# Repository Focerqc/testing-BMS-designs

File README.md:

# Testing BMS designs

Experimental battery-management hardware, built in public. The first design is an
**18S cell-monitoring slave module** based on the Analog Devices **ADBMS1818**,
talking to a separate, bought master over isoSPI.

> Engineering drafts. Nothing here is validated for manufacture or use on a real pack.

## Status (2026-11-13)

| | **18S Guard** (`slave-18s/`) | **18S Lean** (`slave-18s-lean/`) |
|---|---|---|
| Purpose | Hot-plug harnesses, unknown packs, bench work | One known 18S pack, harness plugged in once |
| Schematic | Complete, ERC 0 / 0 | Generated from Guard, ERC 0 / 0 |
| PCB | 120 × 70 mm placeholder, parts grouped, **not routed** | **70 × 32 mm, 4 layers, fully routed**, every part on the front |
| Ready to order | No | **No.** The isoSPI area is being re-planned (see below) |

Lean is the board being worked on. Guard is its source: Lean's schematic is generated from
Guard by `_tools/kicad_sch/make_lean.py` and is never edited by hand.

### Lean at a glance

- 77 footprints, 88 nets, single-sided assembly, four M2 holes.
- Cell plugs: JST PH, **10 + 9 pins**. J1 carries C0–C9 and J5 carries C10–C18, so C9 comes in
  on one wire and the two plugs can be told apart.
- Per cell: a 10 Ω 0402 series resistor and a 120 Ω 1206 balance resistor (about 31 mA and
  0.12 W at 4.2 V) through the chip's internal switches.
- Regulator: FZT853 (SOT-223) driven by the chip, with a 1 kΩ 1 W collector resistor that
  takes part of the heat off the transistor.
- isoSPI: two Bourns SM91502AL transformers, split 2 × 51 Ω termination with 10 nF
  centre-tap capacitors, JST GH 2-pin plugs.
- No fuses, clamps, TVS or C-pin capacitors. Those are Guard's.

Its checks on this branch: netlist 239 pins with 0 problems, PCB parity pass, design rules
loaded, and zone-filled DRC with 0 errors, 0 unconnected items and 153 silkscreen warnings.

## What we have learned so far

### 1. A clean DRC does not make an isoSPI layout right

The ADBMS1818 datasheet (Rev. B, p. 86) asks for two things that DRC cannot see: no ground
plane under or between the transformer and its plug, and **no trace crossing an isoSPI line**
unless a ground plane on an inner layer separates them. Lean meets the first with keep-out
rules. For the second we wrote `_tools/kicad_sch/isospi_shield_check.py`.

- The first version of that check reported 6 crossings. It looked only at the transformer
  centre-tap and termination nets and never treated the chip-side pairs (IPA/IMA, IPB/IMB) as
  isoSPI lines. With each port grouped properly it finds **20**: 12 where port A crosses
  port B, and 8 where the top-of-stack supply track (CELL18) crosses either port.
  The lesson: check a checker against the circuit before trusting its number.
- **Rerouting cannot remove them.** Both ports sit side by side in one corner. Port A's pins
  are below port B's on the chip and its transformer is the far one, so port A has to get
  past port B. Port B fills the whole height from its plug at the board edge down to the
  regulator copper, and the rules keep other tracks out from under its transformer. The best
  a reroute can do is 10 crossings.
- The top-of-stack supply has the same problem: it starts above both ports and ends at the
  regulator below them.

### 2. Put the two isoSPI ports at opposite ends

We compared three other slave boards of this kind. Every one of them puts its two isoSPI ports
at **opposite ends of the board**, each plug with its transformer right beside it. Lean is the
only one that groups them. Splitting them means:

- each port runs from its pins to its own end, so the ports never meet;
- the daisy-chain cables leave from opposite ends instead of crossing over the board;
- the regulator and the top-of-stack supply can be kept clear of both ports.

**Planned next step:** a new Lean floorplan with one port at each end. It moves parts, so it
is tried on a scratch copy first.

### 3. What turned 120 × 70 mm into 70 × 32 mm

- Four copper layers instead of two.
- Small series resistors (the 10 Ω parts carry almost no current) and 120 Ω 1206 balance
  resistors instead of 33 Ω 2512.
- Smaller isoSPI transformers, GH plugs, M2 holes and no test points.
- Leaving out the hot-plug protection, which is the Guard/Lean split.
- Routing planned as lanes before any track is drawn, then written by script from the pad
  positions (`lean_place.py`, `lean_route.py`), so a placement change can be routed and
  checked again in minutes.

### 4. The regulator is a heat question, not a fit question

At 75.6 V the linear regulator dissipates about 1.55 W at 22 mA and 2.5 W at 35 mA, whatever
the package. The 1 kΩ collector resistor only moves part of that off the transistor (about
0.48 W of the 1.55 W). Whether the board stays cool enough is still open. It needs the
master's real duty cycle or a measurement.

### 5. Working method

- One source schematic and generated variants. Part swaps for Lean live in one table.
- `kicad-cli` is the ground truth for netlist, ERC and DRC. Every schematic or PCB change is
  followed by the same scripted checks (below).
- Size and placement changes are tried on a scratch copy before the real board.
- The tool-by-tool lessons are in [AGENTS.md](AGENTS.md).

## Open before Lean can be ordered

- [ ] isoSPI floorplan with the ports at opposite ends, then 0 crossings in the check.
- [ ] Regulator thermal acceptance (see 4).
- [ ] The assembler's acceptance of the open 0.2 mm vias in the chip's exposed pad.
- [ ] Silkscreen cleanup (153 warnings).
- [ ] Harness: match the plug pin order to the pack's tap and thermistor wiring. Seen from
      above with the cell plugs along the top edge, pin 1 of both is at the left end.
- [ ] Bench test with a cell simulator and one master. Hot-plugging is not qualified on Lean.

The full list, with reasons and dates, is in
[docs/slave-18s-design-basis.md](docs/slave-18s-design-basis.md).

## Checks

```
"C:\Program Files\KiCad\10.0\bin\python.exe" _tools/kicad_sch/lean_route.py --dry
python _tools/kicad_sch/check_slave18s.py --variant lean
python _tools/kicad_sch/check_pcb_parity.py --variant lean
python _tools/kicad_sch/make_rules.py --variant lean --check
python _tools/kicad_sch/isospi_shield_check.py
```

Then run `kicad-cli pcb drc --severity-all --refill-zones` on the board.

## Layout of this repository

| Path | What it is |
|---|---|
| `slave-18s/` | **18S Guard**: KiCad 10 project with hot-plug protection (fuses, clamps, TVS, C-pin caps, test points) |
| `slave-18s-lean/` | **18S Lean**: the same slave without them, 70 × 32 mm, 4 layers. Schematic generated by `make_lean.py`; placement and routing written by `lean_place.py` and `lean_route.py` |
| `docs/slave-18s-design-basis.md` | Values, reasoning, deviations from the datasheet circuit and open items |
| `docs/slave-18s-lean-layout-plan.md` | Placement and routing plan for Lean, with the check to run after each step |
| `docs/master-ennoid-xlite.md` | The bought master and how the slave fits under it |
| `_tools/kicad_sch/` | Checks, design-rule generator, Lean generator, placement and routing scripts (table in AGENTS.md) |
| `_tools/pcb_dashboard/` | Board Boxes: local KiCad dashboard (top and bottom view, annotate, chip info, fresh 3D renders) |
| `site/` | Published GitHub Pages copy of Board Boxes plus the News page |
| `_reference/` | Datasheets and reference material. The private parts are gitignored |

## Dashboards

- **Local:** double-click `Start Dashboards.cmd` (Python with `requirements.txt`, KiCad 10).
  Opens http://localhost:5180/.
- **Hosted:** https://focerqc.github.io/testing-BMS-designs/ (News at `news.html`).

Refresh the hosted copy:

```
python _tools/pcb_dashboard/export_site.py
node _tools/pcb_dashboard/check_hosted.cjs
```

Then push `site/` to `main`; `.github/workflows/pages.yml` publishes it.

## Roadmap

1. ~~18S slave schematic from the ADBMS1818 typical application.~~ Done.
2. Slave PCB: Lean is routed. Redo its isoSPI floorplan, then order and bench test with a
   resistor-ladder cell simulator and an LTC6820/ESP32 dongle.
3. Carrier PCB taking two slaves (target slot 156.5 × 37 × 10 mm) for a plug-and-play harness.
4. Master: bought, not designed here (see `docs/master-ennoid-xlite.md`).

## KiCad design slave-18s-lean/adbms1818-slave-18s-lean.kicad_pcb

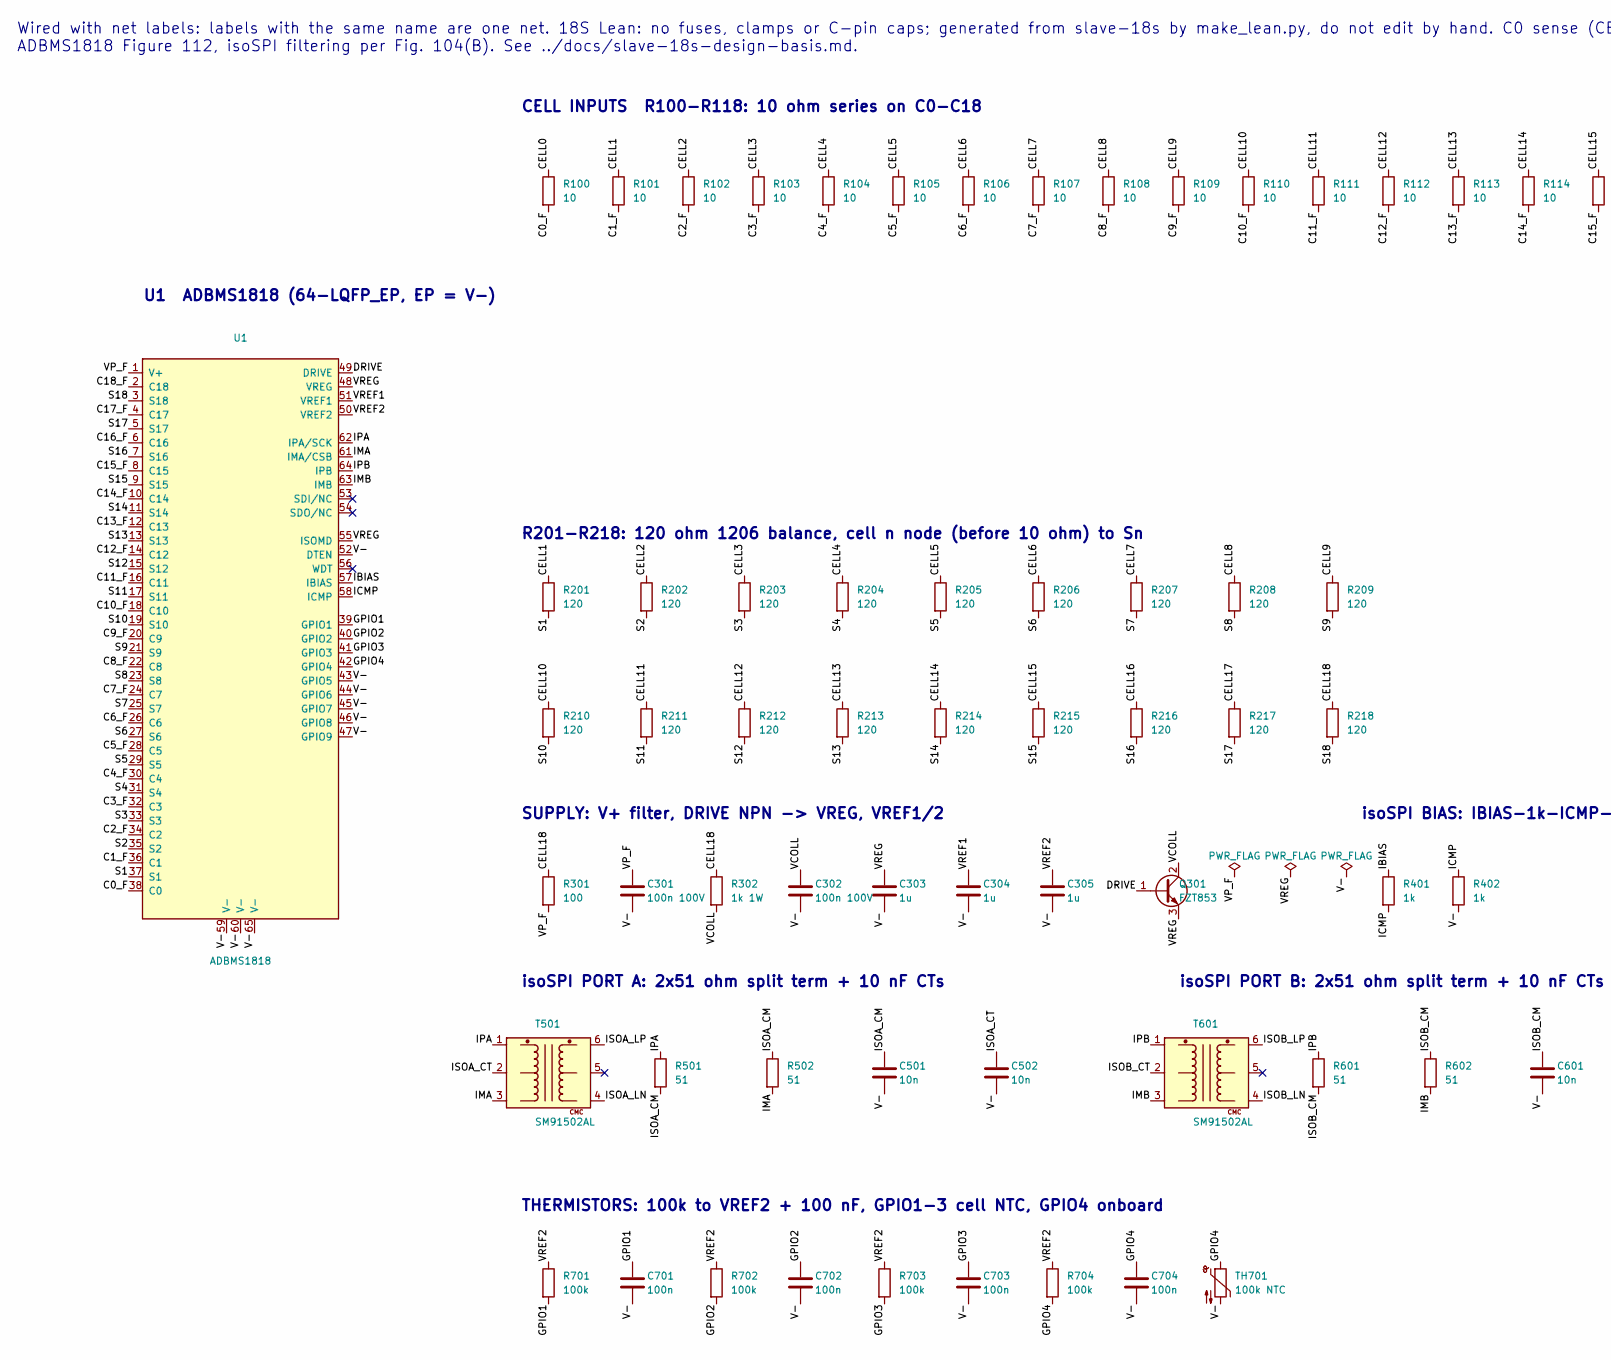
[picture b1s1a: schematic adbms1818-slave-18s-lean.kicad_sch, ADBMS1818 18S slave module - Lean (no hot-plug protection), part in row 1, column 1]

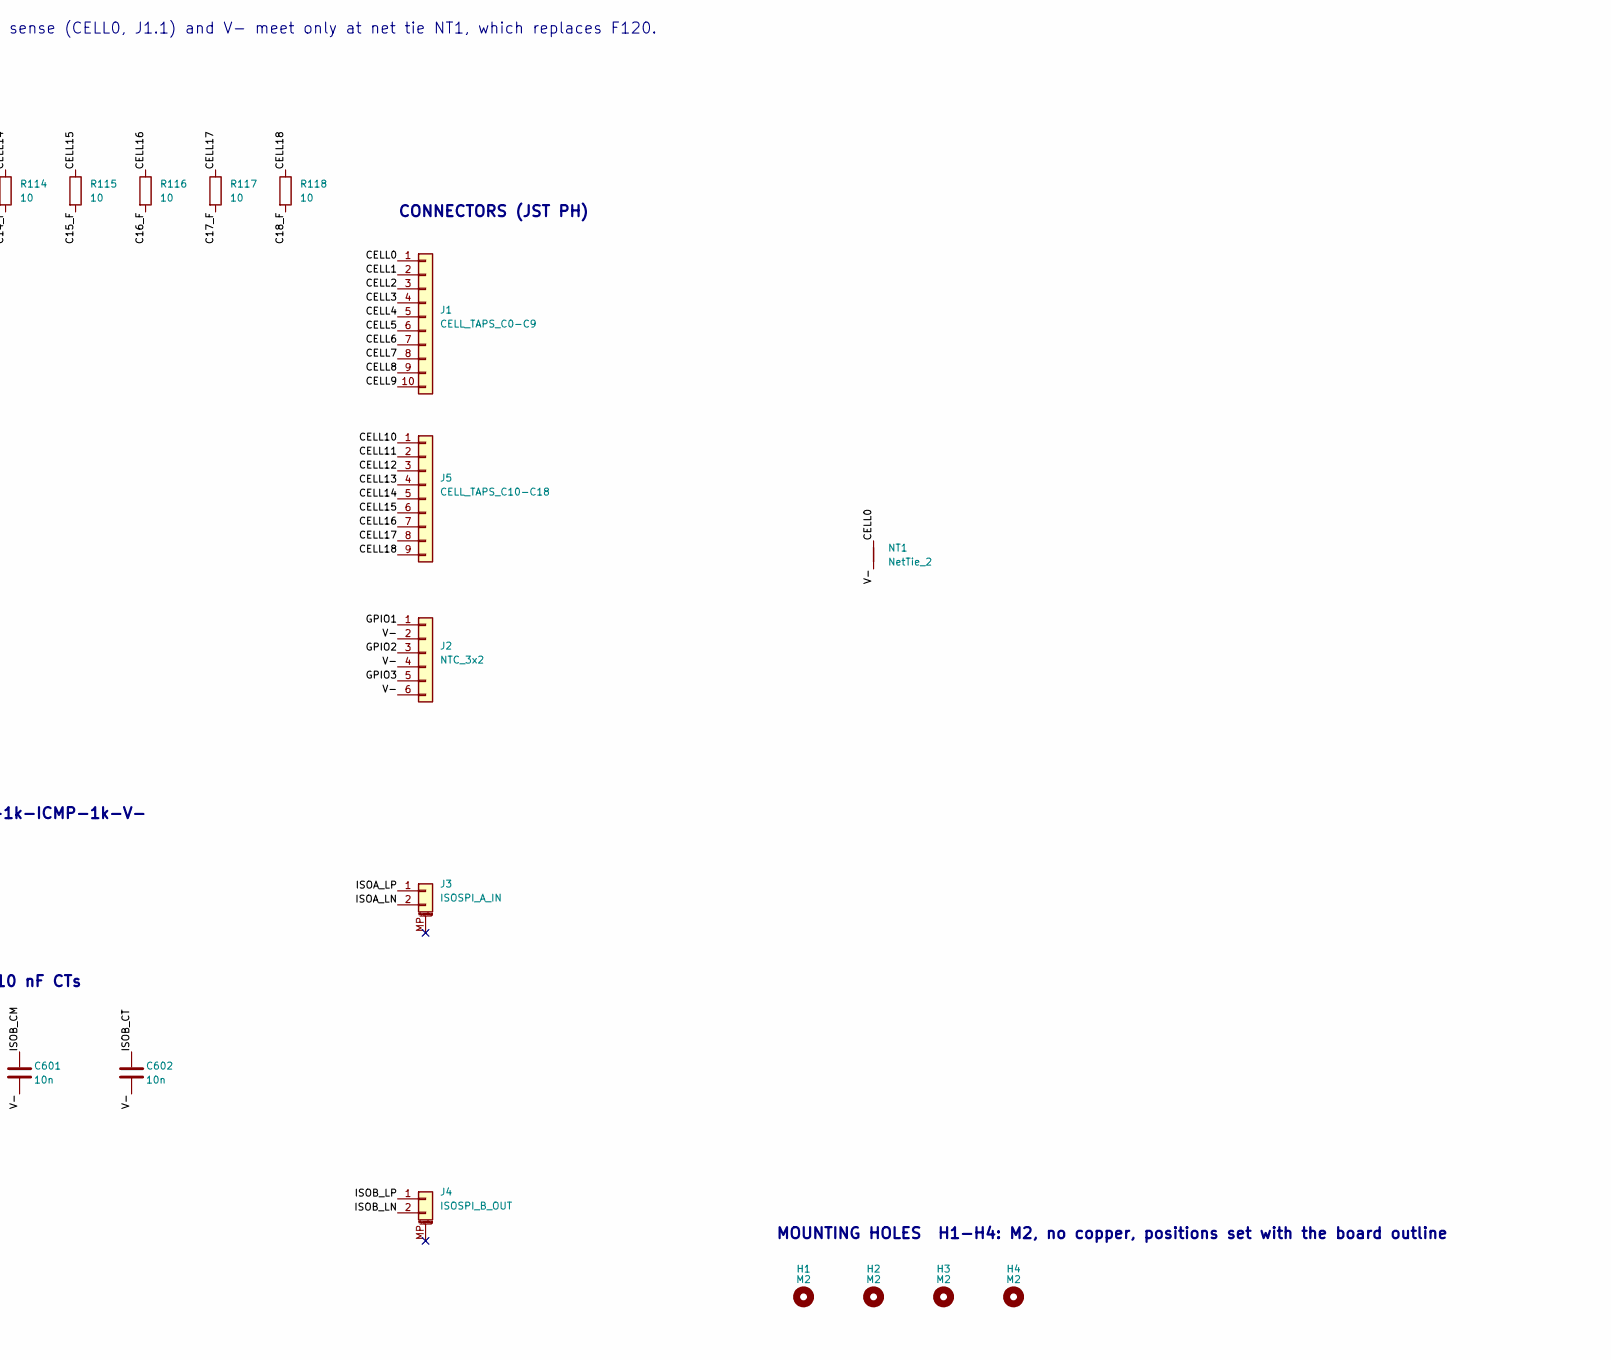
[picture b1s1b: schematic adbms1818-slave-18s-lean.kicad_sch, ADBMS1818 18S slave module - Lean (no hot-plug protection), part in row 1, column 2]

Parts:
C301, C302: 100n 100V; C_0805_2012Metric; MPN CL21B104KCFNNNE; LCSC C28233
C303, C304, C305: 1u; C_0603_1608Metric; MPN CL10A105KB8NNNC; LCSC C15849
C501, C502: 10n; C_0603_1608Metric; MPN 0603B103K500NT; LCSC C57112
C601, C602: 10n; C_0402_1005Metric; MPN CL05B103KB5NNNC; LCSC C15195
C701, C702, C703, C704: 100n; C_0603_1608Metric; MPN CC0603KRX7R9BB104; LCSC C14663
H1, H2, H3, H4: M2; MountingHole_2.2mm_M2
J1: CELL_TAPS_C0-C9; JST_PH_B10B-PH-K_1x10_P2.00mm_Vertical; MPN B10B-PH-K-S(LF)(SN); LCSC C158038
J2: NTC_3x2; JST_PH_B6B-PH-K_1x06_P2.00mm_Vertical; MPN B6B-PH-K-S(LF)(SN); LCSC C131342
J3: ISOSPI_A_IN; JST_GH_BM02B-GHS-TBT_1x02-1MP_P1.25mm_Vertical; MPN BM02B-GHS-TBT(LF)(SN); LCSC C161690
J4: ISOSPI_B_OUT; JST_GH_BM02B-GHS-TBT_1x02-1MP_P1.25mm_Vertical; MPN BM02B-GHS-TBT(LF)(SN); LCSC C161690
J5: CELL_TAPS_C10-C18; JST_PH_B9B-PH-K_1x09_P2.00mm_Vertical; MPN B9B-PH-K-S(LF)(SN); LCSC C157968
NT1: NetTie_2; NetTie-2_SMD_Pad0.5mm
Q301: FZT853; SOT-223-3_TabPin2; MPN FZT853TA; LCSC C435890
R100, R101, R102, R103, R104, R105, R106, R107, R108, R109, R110, R111, R112, R113, R114, R115, R116, R117, R118: 10; R_0402_1005Metric; MPN 0402WGF100JTCE; LCSC C25077
R201, R202, R203, R204, R205, R206, R207, R208, R209, R210, R211, R212, R213, R214, R215, R216, R217, R218: 120; R_1206_3216Metric; MPN 1206W4F1200T5E; LCSC C17909
R301: 100; R_0603_1608Metric; MPN 0603WAF1000T5E; LCSC C22775
R302: 1k 1W; R_2512_6332Metric; MPN 25121WF1001T4E; LCSC C54315
R401, R402: 1k; R_0603_1608Metric; MPN 0603WAF1001T5E; LCSC C21190
R501, R502: 51; R_0603_1608Metric; MPN 0603WAF510JT5E; LCSC C23197
R601, R602: 51; R_0402_1005Metric; MPN 0402WGF510JTCE; LCSC C25125
R701, R702, R703, R704: 100k; R_0603_1608Metric; MPN 0603WAF1003T5E; LCSC C25803
T501, T601: SM91502AL; Bourns_SM91502AL; MPN SM91502ALE; LCSC C915690
TH701: 100k NTC; R_0603_1608Metric; MPN NCP18WF104F12RB; LCSC C71280
U1: ADBMS1818; LQFP-64-1EP_10x10mm_P0.5mm_EP5x5mm_ThermalVias; MPN ADBMS1818ASWAZ-RL; LCSC C5372802

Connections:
/C0_F: R100.2, U1.38 (C0)
/C1_F: R101.2, U1.36 (C1)
/C2_F: R102.2, U1.34 (C2)
/C3_F: R103.2, U1.32 (C3)
/C4_F: R104.2, U1.30 (C4)
/C5_F: R105.2, U1.28 (C5)
/C6_F: R106.2, U1.26 (C6)
/C7_F: R107.2, U1.24 (C7)
/C8_F: R108.2, U1.22 (C8)
/C9_F: R109.2, U1.20 (C9)
/C10_F: R110.2, U1.18 (C10)
/C11_F: R111.2, U1.16 (C11)
/C12_F: R112.2, U1.14 (C12)
/C13_F: R113.2, U1.12 (C13)
/C14_F: R114.2, U1.10 (C14)
/C15_F: R115.2, U1.8 (C15)
/C16_F: R116.2, U1.6 (C16)
/C17_F: R117.2, U1.4 (C17)
/C18_F: R118.2, U1.2 (C18)
/CELL0: J1.1, NT1.1, R100.1
/CELL1: J1.2, R101.1, R201.1
/CELL2: J1.3, R102.1, R202.1
/CELL3: J1.4, R103.1, R203.1
/CELL4: J1.5, R104.1, R204.1
/CELL5: J1.6, R105.1, R205.1
/CELL6: J1.7, R106.1, R206.1
/CELL7: J1.8, R107.1, R207.1
/CELL8: J1.9, R108.1, R208.1
/CELL9: J1.10, R109.1, R209.1
/CELL10: J5.1, R110.1, R210.1
/CELL11: J5.2, R111.1, R211.1
/CELL12: J5.3, R112.1, R212.1
/CELL13: J5.4, R113.1, R213.1
/CELL14: J5.5, R114.1, R214.1
/CELL15: J5.6, R115.1, R215.1
/CELL16: J5.7, R116.1, R216.1
/CELL17: J5.8, R117.1, R217.1
/CELL18: J5.9, R118.1, R218.1, R301.1, R302.1
/DRIVE: Q301.1 (B), U1.49 (DRIVE)
/GPIO1: C701.1, J2.1, R701.2, U1.39 (GPIO1)
/GPIO2: C702.1, J2.3, R702.2, U1.40 (GPIO2)
/GPIO3: C703.1, J2.5, R703.2, U1.41 (GPIO3)
/GPIO4: C704.1, R704.2, TH701.1, U1.42 (GPIO4)
/IBIAS: R401.1, U1.57 (IBIAS)
/ICMP: R401.2, R402.1, U1.58 (ICMP)
/IMA: R502.2, T501.3 (PHY-), U1.61 (IMA/CSB)
/IMB: R602.2, T601.3 (PHY-), U1.63 (IMB)
/IPA: R501.1, T501.1 (PHY+), U1.62 (IPA/SCK)
/IPB: R601.1, T601.1 (PHY+), U1.64 (IPB)
/ISOA_CM: C501.1, R501.2, R502.1
/ISOA_CT: C502.1, T501.2 (PHY_CT)
/ISOA_LN: J3.2, T501.4 (LINE-)
/ISOA_LP: J3.1, T501.6 (LINE+)
/ISOB_CM: C601.1, R601.2, R602.1
/ISOB_CT: C602.1, T601.2 (PHY_CT)
/ISOB_LN: J4.2, T601.4 (LINE-)
/ISOB_LP: J4.1, T601.6 (LINE+)
/S1: R201.2, U1.37 (S1)
/S2: R202.2, U1.35 (S2)
/S3: R203.2, U1.33 (S3)
/S4: R204.2, U1.31 (S4)
/S5: R205.2, U1.29 (S5)
/S6: R206.2, U1.27 (S6)
/S7: R207.2, U1.25 (S7)
/S8: R208.2, U1.23 (S8)
/S9: R209.2, U1.21 (S9)
/S10: R210.2, U1.19 (S10)
/S11: R211.2, U1.17 (S11)
/S12: R212.2, U1.15 (S12)
/S13: R213.2, U1.13 (S13)
/S14: R214.2, U1.11 (S14)
/S15: R215.2, U1.9 (S15)
/S16: R216.2, U1.7 (S16)
/S17: R217.2, U1.5 (S17)
/S18: R218.2, U1.3 (S18)
/V-: C301.2, C302.2, C303.2, C304.2, C305.2, C501.2, C502.2, C601.2, C602.2, C701.2, C702.2, C703.2, C704.2, J2.2, J2.4, J2.6, NT1.2, R402.2, TH701.2, U1.43 (GPIO5), U1.44 (GPIO6), U1.45 (GPIO7), U1.46 (GPIO8), U1.47 (GPIO9), U1.52 (DTEN), U1.59 (V-), U1.60 (V-), U1.65 (V-)
/VCOLL: C302.1, Q301.2 (C), R302.2
/VP_F: C301.1, R301.2, U1.1 (V+)
/VREF1: C304.1, U1.51 (VREF1)
/VREF2: C305.1, R701.1, R702.1, R703.1, R704.1, U1.50 (VREF2)
/VREG: C303.1, Q301.3 (E), U1.48 (VREG), U1.55 (ISOMD)

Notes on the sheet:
R201-R218: 120 ohm 1206 balance, cell n node (before 10 ohm) to Sn
CONNECTORS (JST PH)
CELL INPUTS R100-R118: 10 ohm series on C0-C18
Wired with net labels: labels with the same name are one net. 18S Lean: no fuses, clamps or C-pin caps; generated from slave-18s by make_lean.py, do not edit by hand. C0 sense (CELL0, J1.1) and V- meet only at net tie NT1, which replaces F120. ADBMS1818 Figure 112, isoSPI filtering per Fig. 104(B).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
THERMISTORS: 100k to VREF2 + 100 nF, GPIO1-3 cell NTC, GPIO4 onboard
isoSPI BIAS: IBIAS-1k-ICMP-1k-V-
U1 ADBMS1818 (64-LQFP_EP, EP = V-)
MOUNTING HOLES H1-H4: M2, no copper, positions set with the board outline
isoSPI PORT A: 2x51 ohm split term + 10 nF CTs
isoSPI PORT B: 2x51 ohm split term + 10 nF CTs
SUPPLY: V+ filter, DRIVE NPN -> VREG, VREF1/2

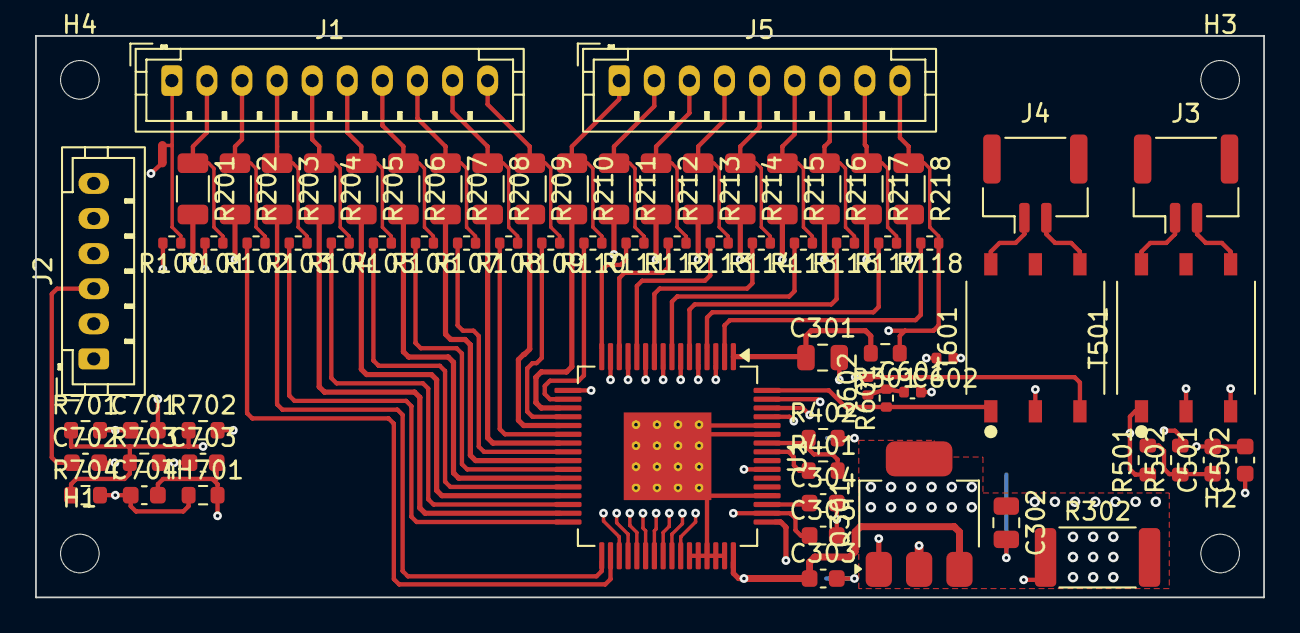
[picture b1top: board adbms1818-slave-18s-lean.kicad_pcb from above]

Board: 4 copper layers, 70.0 x 32.0 mm, 77 parts (0 on the bottom side), 81 nets.

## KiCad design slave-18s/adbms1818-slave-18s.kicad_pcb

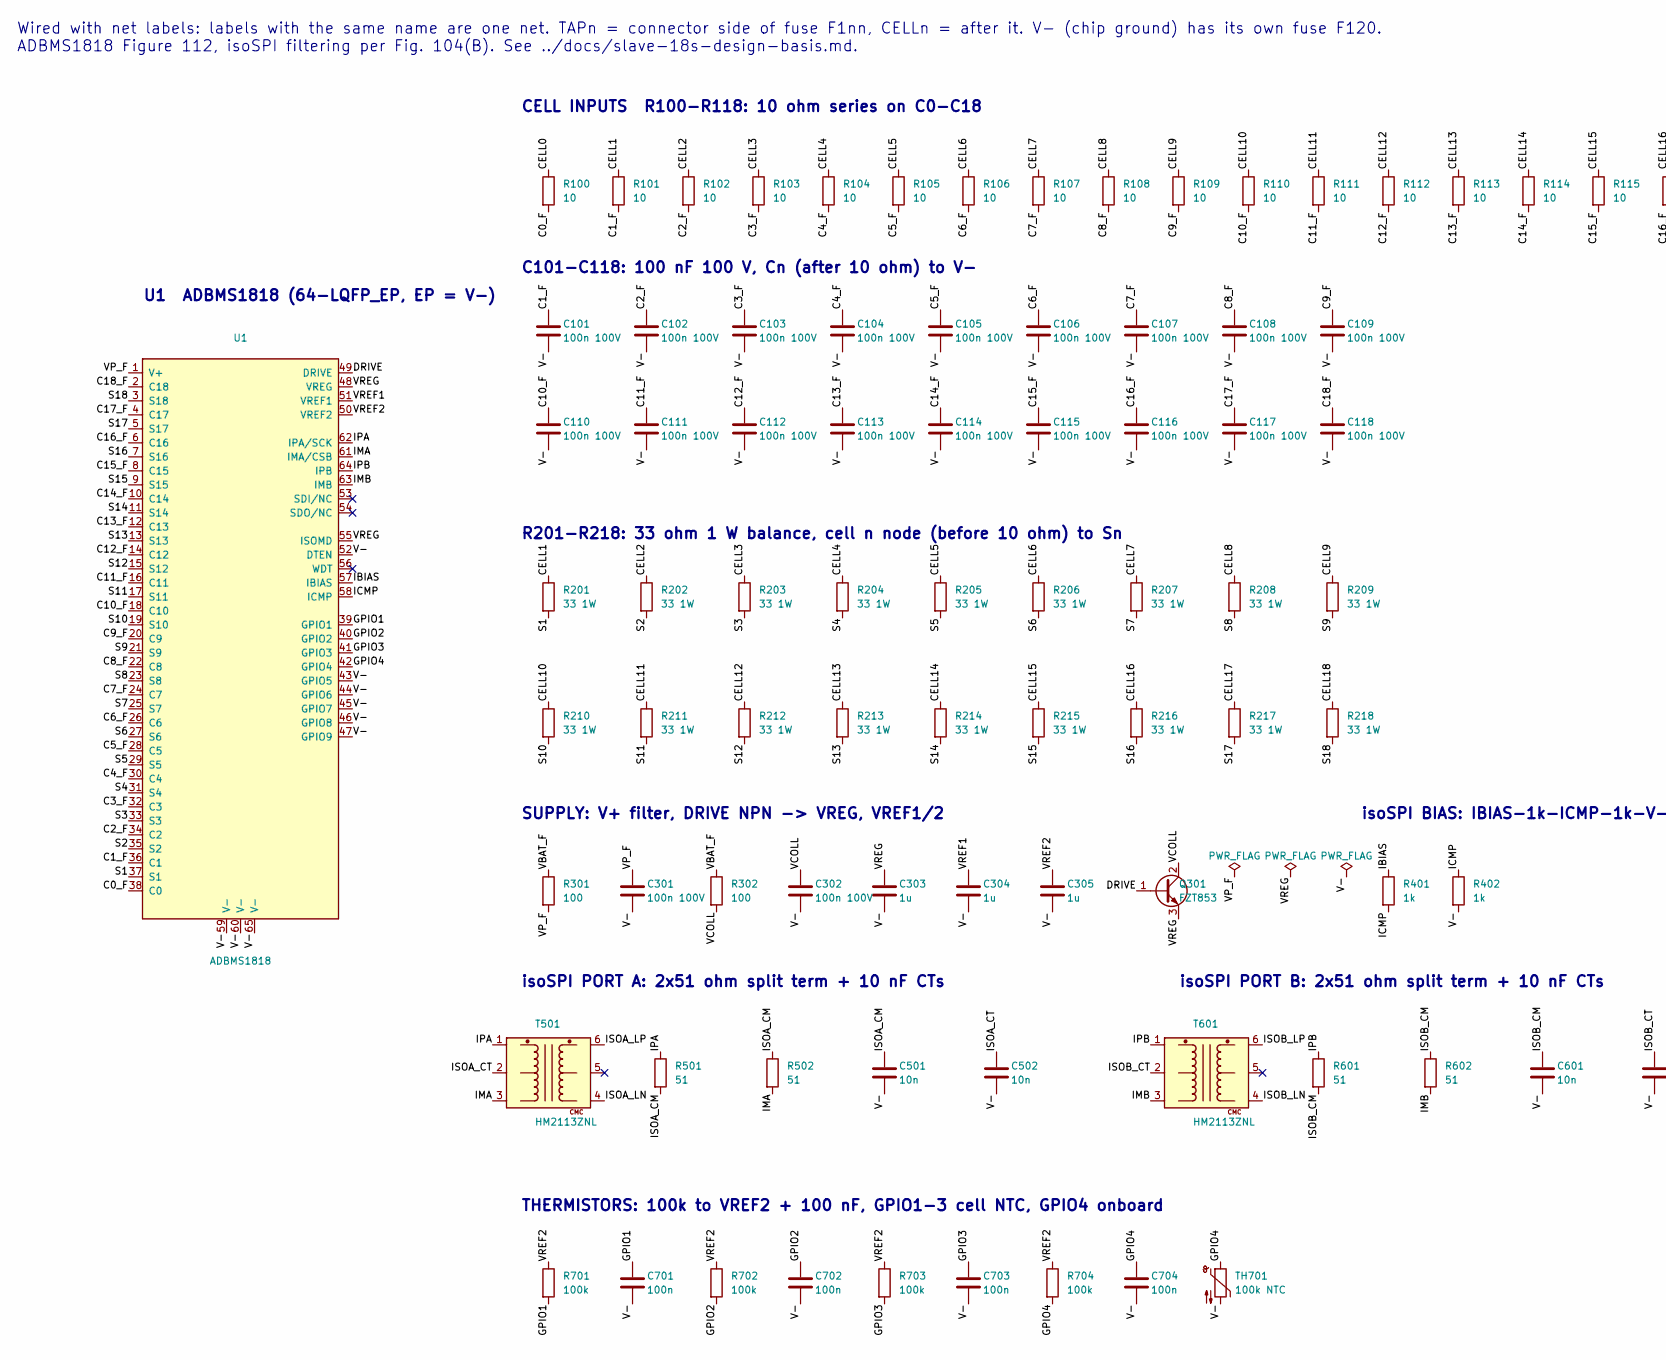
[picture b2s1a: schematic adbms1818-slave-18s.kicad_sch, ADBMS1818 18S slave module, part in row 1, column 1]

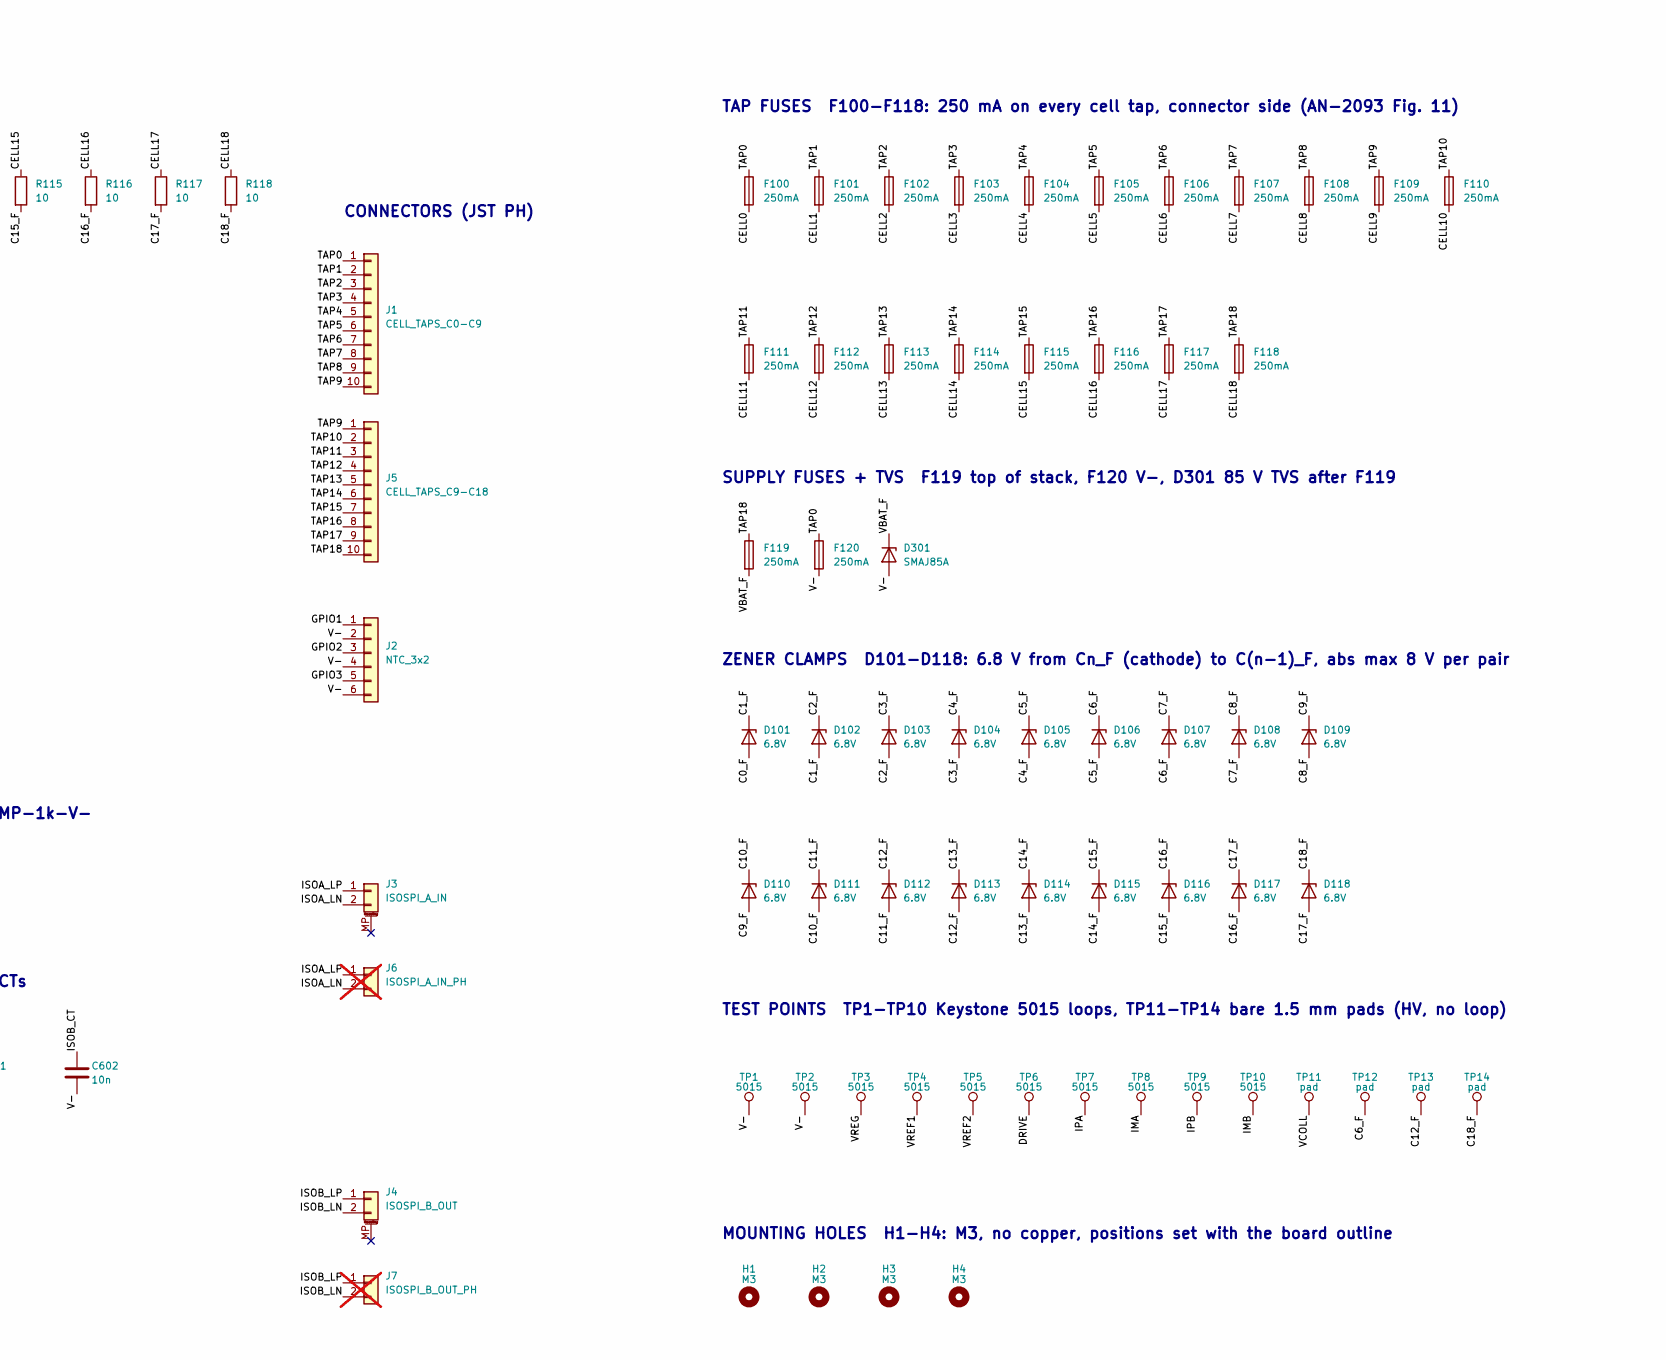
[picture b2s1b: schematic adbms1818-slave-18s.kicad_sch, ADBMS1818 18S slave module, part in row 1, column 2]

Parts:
C101, C102, C103, C104, C105, C106, C107, C108, C109, C110, C111, C112, C113, C114, C115, C116, C117, C118, C301, C302: 100n 100V; C_0805_2012Metric; MPN CL21B104KCFNNNE; LCSC C28233
C303, C304, C305: 1u; C_0603_1608Metric; MPN CL10A105KB8NNNC; LCSC C15849
C501, C502, C601, C602: 10n; C_0603_1608Metric; MPN 0603B103K500NT; LCSC C57112
C701, C702, C703, C704: 100n; C_0603_1608Metric; MPN CC0603KRX7R9BB104; LCSC C14663
D101, D102, D103, D104, D105, D106, D107, D108, D109, D110, D111, D112, D113, D114, D115, D116, D117, D118: 6.8V; D_SOD-123; MPN BZT52C6V8; LCSC C2120
D301: SMAJ85A; D_SMA; MPN SMAJ85A; LCSC C698956
F100, F101, F102, F103, F104, F105, F106, F107, F108, F109, F110, F111, F112, F113, F114, F115, F116, F117, F118, F119, F120: 250mA; Fuse_1206_3216Metric; MPN 0466.250NRHF; LCSC C83557
H1, H2, H3, H4: M3; MountingHole_3.2mm_M3
J1: CELL_TAPS_C0-C9; JST_PH_B10B-PH-K_1x10_P2.00mm_Vertical; MPN B10B-PH-K-S(LF)(SN); LCSC C158038
J2: NTC_3x2; JST_PH_B6B-PH-K_1x06_P2.00mm_Vertical; MPN B6B-PH-K-S(LF)(SN); LCSC C131342
J3: ISOSPI_A_IN; JST_GH_BM02B-GHS-TBT_1x02-1MP_P1.25mm_Vertical; MPN BM02B-GHS-TBT(LF)(SN); LCSC C161690
J4: ISOSPI_B_OUT; JST_GH_BM02B-GHS-TBT_1x02-1MP_P1.25mm_Vertical; MPN BM02B-GHS-TBT(LF)(SN); LCSC C161690
J5: CELL_TAPS_C9-C18; JST_PH_B10B-PH-K_1x10_P2.00mm_Vertical; MPN B10B-PH-K-S(LF)(SN); LCSC C158038
J6: ISOSPI_A_IN_PH; JST_PH_B2B-PH-K_1x02_P2.00mm_Vertical; MPN B2B-PH-K-S(LF)(SN); LCSC C131337; not fitted
J7: ISOSPI_B_OUT_PH; JST_PH_B2B-PH-K_1x02_P2.00mm_Vertical; MPN B2B-PH-K-S(LF)(SN); LCSC C131337; not fitted
Q301: FZT853; SOT-223-3_TabPin2; MPN FZT853TA; LCSC C435890
R100, R101, R102, R103, R104, R105, R106, R107, R108, R109, R110, R111, R112, R113, R114, R115, R116, R117, R118: 10; R_1206_3216Metric; MPN 1206W4F100JT5E; LCSC C17903
R201, R202, R203, R204, R205, R206, R207, R208, R209, R210, R211, R212, R213, R214, R215, R216, R217, R218: 33 1W; R_2512_6332Metric; MPN 25121WF330JT4E; LCSC C53728
R301: 100; R_0603_1608Metric; MPN 0603WAF1000T5E; LCSC C22775
R302: 100; R_0805_2012Metric; MPN 0805W8F1000T5E; LCSC C17408
R401, R402: 1k; R_0603_1608Metric; MPN 0603WAF1001T5E; LCSC C21190
R501, R502, R601, R602: 51; R_0603_1608Metric; MPN 0603WAF510JT5E; LCSC C23197
R701, R702, R703, R704: 100k; R_0603_1608Metric; MPN 0603WAF1003T5E; LCSC C25803
T501, T601: HM2113ZNL; Pulse_HM2113ZNL; MPN HM2113ZNLT; LCSC C5730533
TH701: 100k NTC; R_0603_1608Metric; MPN NCP18WF104F12RB; LCSC C71280
TP1, TP2, TP3, TP4, TP5, TP6, TP7, TP8, TP9, TP10: 5015; TestPoint_Keystone_5015_Micro_Mini; MPN 5015; LCSC C2906768
TP11, TP12, TP13, TP14: pad; TestPoint_Pad_D1.5mm
U1: ADBMS1818; LQFP-64-1EP_10x10mm_P0.5mm_EP5x5mm_ThermalVias; MPN ADBMS1818ASWAZ-RL; LCSC C5372802

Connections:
/C0_F: D101.2 (A), R100.2, U1.38 (C0)
/C1_F: C101.1, D101.1 (K), D102.2 (A), R101.2, U1.36 (C1)
/C2_F: C102.1, D102.1 (K), D103.2 (A), R102.2, U1.34 (C2)
/C3_F: C103.1, D103.1 (K), D104.2 (A), R103.2, U1.32 (C3)
/C4_F: C104.1, D104.1 (K), D105.2 (A), R104.2, U1.30 (C4)
/C5_F: C105.1, D105.1 (K), D106.2 (A), R105.2, U1.28 (C5)
/C6_F: C106.1, D106.1 (K), D107.2 (A), R106.2, TP12.1 (1_1), U1.26 (C6)
/C7_F: C107.1, D107.1 (K), D108.2 (A), R107.2, U1.24 (C7)
/C8_F: C108.1, D108.1 (K), D109.2 (A), R108.2, U1.22 (C8)
/C9_F: C109.1, D109.1 (K), D110.2 (A), R109.2, U1.20 (C9)
/C10_F: C110.1, D110.1 (K), D111.2 (A), R110.2, U1.18 (C10)
/C11_F: C111.1, D111.1 (K), D112.2 (A), R111.2, U1.16 (C11)
/C12_F: C112.1, D112.1 (K), D113.2 (A), R112.2, TP13.1 (1_1), U1.14 (C12)
/C13_F: C113.1, D113.1 (K), D114.2 (A), R113.2, U1.12 (C13)
/C14_F: C114.1, D114.1 (K), D115.2 (A), R114.2, U1.10 (C14)
/C15_F: C115.1, D115.1 (K), D116.2 (A), R115.2, U1.8 (C15)
/C16_F: C116.1, D116.1 (K), D117.2 (A), R116.2, U1.6 (C16)
/C17_F: C117.1, D117.1 (K), D118.2 (A), R117.2, U1.4 (C17)
/C18_F: C118.1, D118.1 (K), R118.2, TP14.1 (1_1), U1.2 (C18)
/CELL0: F100.2, R100.1
/CELL1: F101.2, R101.1, R201.1
/CELL2: F102.2, R102.1, R202.1
/CELL3: F103.2, R103.1, R203.1
/CELL4: F104.2, R104.1, R204.1
/CELL5: F105.2, R105.1, R205.1
/CELL6: F106.2, R106.1, R206.1
/CELL7: F107.2, R107.1, R207.1
/CELL8: F108.2, R108.1, R208.1
/CELL9: F109.2, R109.1, R209.1
/CELL10: F110.2, R110.1, R210.1
/CELL11: F111.2, R111.1, R211.1
/CELL12: F112.2, R112.1, R212.1
/CELL13: F113.2, R113.1, R213.1
/CELL14: F114.2, R114.1, R214.1
/CELL15: F115.2, R115.1, R215.1
/CELL16: F116.2, R116.1, R216.1
/CELL17: F117.2, R117.1, R217.1
/CELL18: F118.2, R118.1, R218.1
/DRIVE: Q301.1 (B), TP6.1 (1_1), U1.49 (DRIVE)
/GPIO1: C701.1, J2.1, R701.2, U1.39 (GPIO1)
/GPIO2: C702.1, J2.3, R702.2, U1.40 (GPIO2)
/GPIO3: C703.1, J2.5, R703.2, U1.41 (GPIO3)
/GPIO4: C704.1, R704.2, TH701.1, U1.42 (GPIO4)
/IBIAS: R401.1, U1.57 (IBIAS)
/ICMP: R401.2, R402.1, U1.58 (ICMP)
/IMA: R502.2, T501.3 (PHY-), TP8.1 (1_1), U1.61 (IMA/CSB)
/IMB: R602.2, T601.3 (PHY-), TP10.1 (1_1), U1.63 (IMB)
/IPA: R501.1, T501.1 (PHY+), TP7.1 (1_1), U1.62 (IPA/SCK)
/IPB: R601.1, T601.1 (PHY+), TP9.1 (1_1), U1.64 (IPB)
/ISOA_CM: C501.1, R501.2, R502.1
/ISOA_CT: C502.1, T501.2 (PHY_CT)
/ISOA_LN: J3.2, J6.2, T501.4 (LINE-)
/ISOA_LP: J3.1, J6.1, T501.6 (LINE+)
/ISOB_CM: C601.1, R601.2, R602.1
/ISOB_CT: C602.1, T601.2 (PHY_CT)
/ISOB_LN: J4.2, J7.2, T601.4 (LINE-)
/ISOB_LP: J4.1, J7.1, T601.6 (LINE+)
/S1: R201.2, U1.37 (S1)
/S2: R202.2, U1.35 (S2)
/S3: R203.2, U1.33 (S3)
/S4: R204.2, U1.31 (S4)
/S5: R205.2, U1.29 (S5)
/S6: R206.2, U1.27 (S6)
/S7: R207.2, U1.25 (S7)
/S8: R208.2, U1.23 (S8)
/S9: R209.2, U1.21 (S9)
/S10: R210.2, U1.19 (S10)
/S11: R211.2, U1.17 (S11)
/S12: R212.2, U1.15 (S12)
/S13: R213.2, U1.13 (S13)
/S14: R214.2, U1.11 (S14)
/S15: R215.2, U1.9 (S15)
/S16: R216.2, U1.7 (S16)
/S17: R217.2, U1.5 (S17)
/S18: R218.2, U1.3 (S18)
/TAP0: F100.1, F120.1, J1.1
/TAP1: F101.1, J1.2
/TAP2: F102.1, J1.3
/TAP3: F103.1, J1.4
/TAP4: F104.1, J1.5
/TAP5: F105.1, J1.6
/TAP6: F106.1, J1.7
/TAP7: F107.1, J1.8
/TAP8: F108.1, J1.9
/TAP9: F109.1, J1.10, J5.1
/TAP10: F110.1, J5.2
/TAP11: F111.1, J5.3
/TAP12: F112.1, J5.4
/TAP13: F113.1, J5.5
/TAP14: F114.1, J5.6
/TAP15: F115.1, J5.7
/TAP16: F116.1, J5.8
/TAP17: F117.1, J5.9
/TAP18: F118.1, F119.1, J5.10
/V-: C101.2, C102.2, C103.2, C104.2, C105.2, C106.2, C107.2, C108.2, C109.2, C110.2, C111.2, C112.2, C113.2, C114.2, C115.2, C116.2, C117.2, C118.2, C301.2, C302.2, C303.2, C304.2, C305.2, C501.2, C502.2, C601.2, C602.2, C701.2, C702.2, C703.2, C704.2, D301.2 (A), F120.2, J2.2, J2.4, J2.6, R402.2, TH701.2, TP1.1 (1_1), TP2.1 (1_1), U1.43 (GPIO5), U1.44 (GPIO6), U1.45 (GPIO7), U1.46 (GPIO8), U1.47 (GPIO9), U1.52 (DTEN), U1.59 (V-), U1.60 (V-), U1.65 (V-)
/VBAT_F: D301.1 (K), F119.2, R301.1, R302.1
/VCOLL: C302.1, Q301.2 (C), R302.2, TP11.1 (1_1)
/VP_F: C301.1, R301.2, U1.1 (V+)
/VREF1: C304.1, TP4.1 (1_1), U1.51 (VREF1)
/VREF2: C305.1, R701.1, R702.1, R703.1, R704.1, TP5.1 (1_1), U1.50 (VREF2)
/VREG: C303.1, Q301.3 (E), TP3.1 (1_1), U1.48 (VREG), U1.55 (ISOMD)

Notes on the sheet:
ZENER CLAMPS D101-D118: 6.8 V from Cn_F (cathode) to C(n-1)_F, abs max 8 V per pair
TAP FUSES F100-F118: 250 mA on every cell tap, connector side (AN-2093 Fig. 11)
R201-R218: 33 ohm 1 W balance, cell n node (before 10 ohm) to Sn
CONNECTORS (JST PH)
CELL INPUTS R100-R118: 10 ohm series on C0-C18
C101-C118: 100 nF 100 V, Cn (after 10 ohm) to V-
Wired with net labels: labels with the same name are one net. TAPn = connector side of fuse F1nn, CELLn = after it. V- (chip ground) has its own fuse F120. ADBMS1818 Figure 112, isoSPI filtering per Fig. 104(B). See ../docs/slave-18s-design-basis.md.
TEST POINTS TP1-TP10 Keystone 5015 loops, TP11-TP14 bare 1.5 mm pads (HV, no loop)
THERMISTORS: 100k to VREF2 + 100 nF, GPIO1-3 cell NTC, GPIO4 onboard
isoSPI BIAS: IBIAS-1k-ICMP-1k-V-
U1 ADBMS1818 (64-LQFP_EP, EP = V-)
SUPPLY FUSES + TVS F119 top of stack, F120 V-, D301 85 V TVS after F119
MOUNTING HOLES H1-H4: M3, no copper, positions set with the board outline
isoSPI PORT A: 2x51 ohm split term + 10 nF CTs
isoSPI PORT B: 2x51 ohm split term + 10 nF CTs
SUPPLY: V+ filter, DRIVE NPN -> VREG, VREF1/2

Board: 2 copper layers, 150 parts (0 on the bottom side), 101 nets, no tracks yet.

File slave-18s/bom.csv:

Comment,Designator,Footprint,LCSC
100n 100V,"C101,C102,C103,C104,C105,C106,C107,C108,C109,C110,C111,C112,C113,C114,C115,C116,C117,C118,C301,C302",C_0805_2012Metric,C28233
1u,"C303,C304,C305",C_0603_1608Metric,C15849
10n,"C501,C502,C601,C602",C_0603_1608Metric,C57112
100n,"C701,C702,C703,C704",C_0603_1608Metric,C14663
B10B-PH-K-S,"J1,J5",JST_PH_B10B-PH-K_1x10_P2.00mm_Vertical,C158038
B6B-PH-K-S,J2,JST_PH_B6B-PH-K_1x06_P2.00mm_Vertical,C131342
BM02B-GHS-TBT,"J3,J4",JST_GH_BM02B-GHS-TBT_1x02-1MP_P1.25mm_Vertical,C161690
FZT853,Q301,SOT-223-3_TabPin2,C435890
10,"R100,R101,R102,R103,R104,R105,R106,R107,R108,R109,R110,R111,R112,R113,R114,R115,R116,R117,R118",R_1206_3216Metric,C17903
33 1W,"R201,R202,R203,R204,R205,R206,R207,R208,R209,R210,R211,R212,R213,R214,R215,R216,R217,R218",R_2512_6332Metric,C53728
100,R301,R_0603_1608Metric,C22775
100,R302,R_0805_2012Metric,C17408
1k,"R401,R402",R_0603_1608Metric,C21190
51,"R501,R502,R601,R602",R_0603_1608Metric,C23197
100k,"R701,R702,R703,R704",R_0603_1608Metric,C25803
HM2113ZNL,"T501,T601",Pulse_HM2113ZNL,C5730533
100k NTC,TH701,R_0603_1608Metric,C71280
ADBMS1818,U1,LQFP-64-1EP_10x10mm_P0.5mm_EP5x5mm_ThermalVias,C5372802
250mA,"F100,F101,F102,F103,F104,F105,F106,F107,F108,F109,F110,F111,F112,F113,F114,F115,F116,F117,F118,F119,F120",Fuse_1206_3216Metric,C83557
6.8V,"D101,D102,D103,D104,D105,D106,D107,D108,D109,D110,D111,D112,D113,D114,D115,D116,D117,D118",D_SOD-123,C2120
SMAJ85A,D301,D_SMA,C698956
5015,"TP1,TP2,TP3,TP4,TP5,TP6,TP7,TP8,TP9,TP10",TestPoint_Keystone_5015_Micro_Mini,C2906768
